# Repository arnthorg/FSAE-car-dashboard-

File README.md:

# A dashboard with rpm bar-graph, gear display, shift-light and oil pressure/  AFR / Speed for RU's 2016 FSAE car 

It's programmed in the arduino environment 

It has:
* engine RPM bargraph, 
* shift light
* OLED display capable if displaying any analog value
* 7-seg gear selected display

Dash-OLED/ contains the main program

PCB/ contains the PCB design

lid/ contains the sketch for the lid that enclosed the electronics

myndir/ contains some images of the project

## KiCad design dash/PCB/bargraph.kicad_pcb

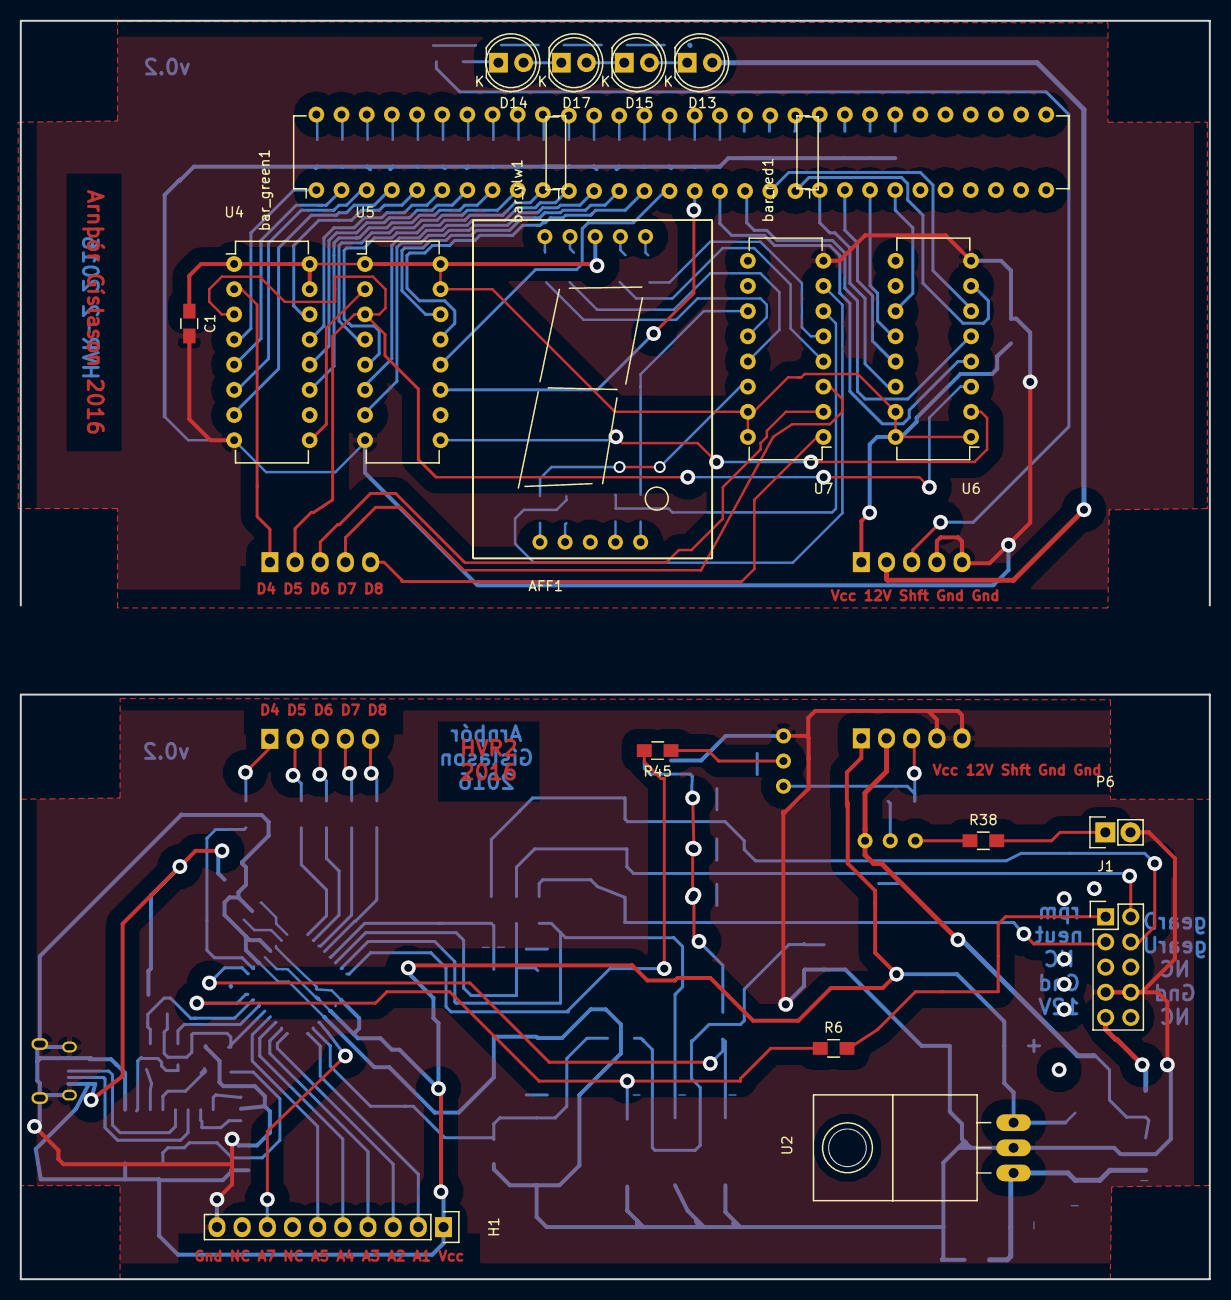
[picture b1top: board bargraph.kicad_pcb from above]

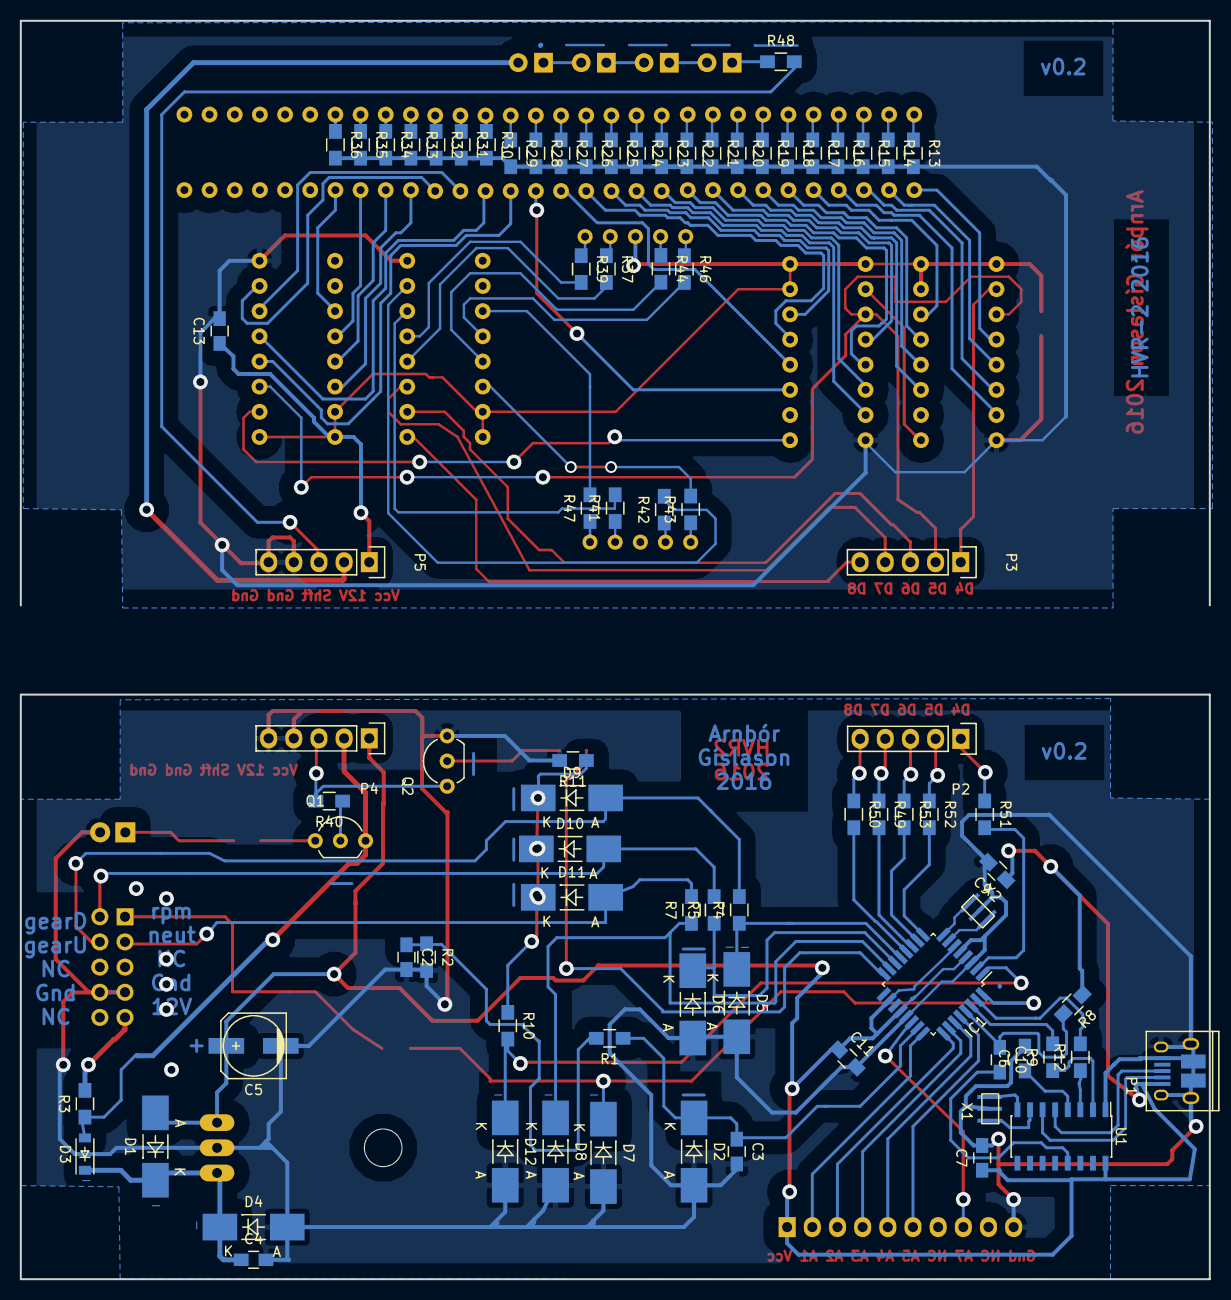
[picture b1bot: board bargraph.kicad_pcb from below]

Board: 2 copper layers, 120.0 x 127.0 mm, 103 parts (83 on the bottom side), 122 nets.

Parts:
AFF1: 7SEGMENTS; 7seg
C1, C6, C7, C9, C10, C11, C13: 100n; C_0805_HandSoldering
C2, C3: C; C_0805_HandSoldering
C4: 470n; C_0805_HandSoldering
C5: 100u; c_elec_6.3x5.8
D1: 1n4007; MELF_Handsoldering
D2, D5, D6, D7, D8, D12: 5.1V; MELF_Handsoldering
D3: D_Schottky_Small; SOD-123
D4: 22V; MELF_Handsoldering
D9, D10, D11: 1n4148; MELF_Handsoldering
D13, D14, D15, D17: LED; LED-5MM
H1: pin_header_10; Pin_Header_Straight_1x10
IC1: ATMEGA328-P; TQFP-32_7x7mm_Pitch0.8mm
J1: DB9; Pin_Header_Straight_2x05
P1: USB_OTG; USB_Micro-B_10103594-0001LF
P2, P4: CONN_01X05; Socket_Strip_Straight_1x05
P3, P5: CONN_01X05; Pin_Header_Straight_1x05
P6: CONN_01X02; Socket_Strip_Straight_1x02
Q1: BC557; TO-92_Inline_Wide
Q2: BC547; TO-92_Inline_Wide
R1, R4, R5, R6, R7, R10: 2k2; R_0805_HandSoldering
R2, R9, R12, R49, R52, R53: 1k; R_0805_HandSoldering
R3: 1; R_0805_HandSoldering
R8, R50: 1kR; R_0805_HandSoldering
R11, R40: 10k; R_0805_HandSoldering
R13, R14, R15, R16, R17, R18, R19, R20, R21, R22, R23, R24, R25, R26, R27, R28, R29, R30, R31, R32, R33, R34, R35, R36, R37, R39, R41, R42, R43, R44, R46, R47: 330; R_0805_HandSoldering
R38: 1R; R_0805_HandSoldering
R45: 2k7; R_0805_HandSoldering
R48: 60R; R_0805_HandSoldering
R51: R; R_0805_HandSoldering
U1: CH340G; SOIC-16_3.9x9.9mm_Pitch1.27mm
U2: LM7805CT; TO-220_Neutral123_Horizontal_LargePads
U4, U5, U6, U7: 74HC4094; DIP-16_W7.62mm
X1, X2: CRYSTAL_SMD; cer_res
bar_green1: DOT-BAR2; DIP-20_W7.62mm
bar_red1: DOT-BAR2; DIP-20_W7.62mm
bar_ylw1: DOT-BAR2; DIP-20_W7.62mm

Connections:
/12vF: D3.2, D13.2, P4.2, P5.2, Q1.3, R3.1
/12vraw: J1.9, R3.2
/A0: C3.1, D2.1, IC1.23, R1.1
/A1: H1.2, IC1.24
/A2: H1.3, IC1.25
/A3: H1.4, IC1.26
/A4: H1.5, IC1.27
/A5: H1.6, IC1.28
/A7: H1.8, IC1.22
/D0: IC1.30, R9.2
/D1: IC1.31, R12.2
/D2: D7.1, IC1.32, R6.1
/D3: D12.1, IC1.1, R10.2
/D4: IC1.2, P3.1, R51.2, U4.2
/D5: IC1.9, P3.2, R52.2, U4.3, U5.3, U6.3
/D6: IC1.10, P3.3, R53.2, U7.2
/D7: IC1.11, P3.4, R49.2, U7.3
/D8: IC1.12, P3.5, R50.2, U7.1
/D9: D5.1, IC1.13, R4.1
/D10: D6.1, IC1.14, R5.1
/D11: D8.1, IC1.15, R7.1
/D12: IC1.16, R45.2
/DTR: C10.2, U1.13
/RST: C10.1, IC1.29, R8.2
/U1_0: U4.4, bar_green1.1
/U1_1: U4.5, bar_green1.2
/U1_2: U4.6, bar_green1.3
/U1_3: U4.7, bar_green1.4
/U1_4: U4.14, bar_green1.5
/U1_5: U4.13, bar_green1.6
/U1_6: U4.12, bar_green1.7
/U1_7: U4.11, bar_green1.8
/U2_0: U5.4, bar_green1.9
/U2_1: U5.5, bar_green1.10
/U2_2: U5.6, bar_ylw1.1
/U2_3: U5.7, bar_ylw1.2
/U2_4: U5.14, bar_ylw1.3
/U2_5: U5.13, bar_ylw1.4
/U2_6: U5.12, bar_ylw1.5
/U2_7: U5.11, bar_ylw1.6
/U3_0: U6.4, bar_ylw1.7
/U3_1: U6.5, bar_ylw1.8
/U3_2: U6.6, bar_ylw1.9
/U3_3: U6.7, bar_ylw1.10
/U3_4: U6.14, bar_red1.1
/U3_5: U6.13, bar_red1.2
/U3_6: U6.12, bar_red1.3
/U3_7: U6.11, bar_red1.4
/Vcc: AFF1.8, C1.1, C5.1, C7.1, C9.1, C11.1, C13.1, D1.2, H1.1, IC1.4, IC1.6, IC1.18, IC1.20, P1.1, P4.1, P5.1, R8.1, U1.16, U2.3, U4.1, U4.15, U4.16, U5.1, U5.15, U5.16, U6.1, U6.15, U6.16, U7.15, U7.16
/extShiftLight: P6.1, R38.2
/gearDown: D10.2, J1.2, R5.2
/gearUp: D9.2, J1.4, R4.2
/intShiftLight: P4.3, P5.3, Q2.1, R40.2, R48.2
/neutral: D11.2, J1.3, R7.2
/oilP: C2.1, R1.2, R2.1
/rpm: J1.1, R6.2
/rx: R9.1, U1.2
/tx: R12.1, U1.3
GNDREF: C1.2, C2.2, C3.2, C4.2, C5.2, C6.2, C7.2, C9.2, C11.2, C13.2, D2.2, D4.2, D5.2, D6.2, D7.2, D8.2, D12.2, H1.10, IC1.3, IC1.5, IC1.21, J1.7, J1.8, P1.5, P1.6, P4.4, P4.5, P5.4, P5.5, P6.2, Q2.3, R2.2, R11.2, R13.2, R14.2, R15.2, R16.2, R17.2, R18.2, R19.2, R20.2, R21.2, R22.2, R23.2, R24.2, R25.2, R26.2, R27.2, R28.2, R29.2, R30.2, R31.2, R32.2, R33.2, R34.2, R35.2, R36.2, U1.1, U2.2, U4.8, U5.8, U6.8, U7.8, X1.2, X2.2
unnamed: AFF1.1, R43.1
unnamed: AFF1.2, R42.1
unnamed: AFF1.4, R41.1
unnamed: AFF1.5, R47.1
unnamed: AFF1.6, R39.1
unnamed: AFF1.7, R37.1
unnamed: AFF1.9, R44.1
unnamed: AFF1.10, R46.1
unnamed: C4.1, D1.1, D3.1, D4.1, U2.1
unnamed: C6.1, U1.4
unnamed: D9.1, D10.1, D11.1, R10.1, R11.1
unnamed: D13.1, D15.2
unnamed: D14.1, R48.1
unnamed: D14.2, D17.1
unnamed: D15.1, D17.2
unnamed: IC1.7, X2.1
unnamed: IC1.8, X2.3
unnamed: P1.2, U1.6
unnamed: P1.3, U1.5
unnamed: P2.1, R51.1
unnamed: P2.2, R52.1
unnamed: P2.3, R53.1
unnamed: P2.4, R49.1
unnamed: P2.5, R50.1
unnamed: Q1.1, R38.1
unnamed: Q1.2, R40.1
unnamed: Q2.2, R45.1
unnamed: R13.1, bar_green1.20
unnamed: R14.1, bar_green1.19
unnamed: R15.1, bar_green1.18
unnamed: R16.1, bar_green1.17
unnamed: R17.1, bar_green1.16
unnamed: R18.1, bar_green1.15
unnamed: R19.1, bar_green1.14
unnamed: R20.1, bar_green1.13
unnamed: R21.1, bar_green1.12
unnamed: R22.1, bar_green1.11
unnamed: R23.1, bar_ylw1.20
unnamed: R24.1, bar_ylw1.19
unnamed: R25.1, bar_ylw1.18
unnamed: R26.1, bar_ylw1.17
unnamed: R27.1, bar_ylw1.16
unnamed: R28.1, bar_ylw1.15
unnamed: R29.1, bar_ylw1.14
unnamed: R30.1, bar_ylw1.13
unnamed: R31.1, bar_ylw1.12
unnamed: R32.1, bar_ylw1.11
unnamed: R33.1, bar_red1.20
unnamed: R34.1, bar_red1.19
unnamed: R35.1, bar_red1.18
unnamed: R36.1, bar_red1.17
unnamed: R37.2, U7.4
unnamed: R39.2, U7.5
unnamed: R41.2, U7.6
unnamed: R42.2, U7.7
unnamed: R43.2, U7.14
unnamed: R44.2, U7.13
unnamed: R46.2, U7.12
unnamed: R47.2, U7.11
unnamed: U1.7, X1.3
unnamed: U1.8, X1.1
unnamed: U4.9, U5.2
unnamed: U5.9, U6.2

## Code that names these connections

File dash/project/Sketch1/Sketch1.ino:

#include "stdbool.h"
#include <avr/wdt.h> // watchdog
#include <EEPROM.h> 
#define interruptPin2 2
#define interruptPin3 3
#define Data 4 // D4
#define CP 5 //   D5
#define Data7 6 //D6
#define CP7 7 
#define Latch7 8 //PORTB tekur við
#define gearUp 9
#define gearDown 10
#define neutral 11 
#define oilP A0
 

const unsigned short MAX_RPM = 9100;
const short BAR_SIZE = 10;
const byte digit[8] = { B00001010, B01100000, B00101010,         //r,1,n,2,3,4,5,E
						B11011010, B11110010, B01100110,
						B10110110, B10011110 };

volatile unsigned long g_lastInterrupt;
volatile unsigned long g_lastInterrupt2;
volatile unsigned short g_pos = 0;
double g_rpm[10] = { 0 };
bool g_barGraphArr[BAR_SIZE] = { 0 };
bool g_periodOn7SegDisp = 0;
volatile short g_selectedGear = 32;


void setup() {

	Serial.begin(9600);
	pinMode(interruptPin2, INPUT);
	pinMode(interruptPin3, INPUT); //external pulldown
	pinMode(neutral, INPUT_PULLUP); //external pulldown
	pinMode(Data, OUTPUT);
	pinMode(CP, OUTPUT);
	pinMode(CP7, OUTPUT);
	pinMode(Data7, OUTPUT);
	pinMode(Latch7, OUTPUT);
	pinMode(gearUp, INPUT);
	pinMode(gearDown, INPUT);
	PORTD &= ~((1 << Data7) | (1 << CP7) | (1 << Latch7)); // unsetting bits, dno if needed
	delay(100); //maybe this delay is important?
	attachInterrupt(digitalPinToInterrupt(interruptPin2), blink, RISING);
	attachInterrupt(digitalPinToInterrupt(interruptPin3), setGear, RISING);
	if (!(PINB & (1 << neutral - 8))) sevenSeg(7); //display E on 7seg
	else {
		g_selectedGear = 2; // 1 being neutral
		sevenSeg(1);
	}
}
// todo: 
// watchdog timer
// skjár
// lesa frá mælum
void loop() {
	
	barGraph(calcRpmAvg());
	//sevenSeg(g_selectedGear); // refresh display periodically
	//Serial.println(g_selectedGear);
}
void setGear() { //int 1
	if (PINB & (1 << (neutral - 8))) {          // 
		g_selectedGear = 2;						//2 being neutral
		return;
	}
	bool gearUpState = (PINB & (1 << (gearUp - 8)));
	bool gearDownState = (PINB & (1 << (gearDown - 8)));
	unsigned long currentInterrupt = micros();
	if ((currentInterrupt - g_lastInterrupt2) > 1.5e5) { //debounce 150ms
		//if ((PINB & (1 << neutral - 8)) && g_selectedGear >6) g_selectedGear = 1; 
		if (gearUpState && g_selectedGear < 6) {
			g_selectedGear++;
		}
		else if (gearDownState && g_selectedGear > 1) {
			g_selectedGear--;
		}
		sevenSeg(g_selectedGear);
		g_lastInterrupt2 = currentInterrupt;
	}
}

void barGraph(int rpm) {
	num2array(rpm);
	for (int iter = 0; iter < BAR_SIZE; iter++) {
		bool x = g_barGraphArr[BAR_SIZE - iter - 1];
		PORTD ^= (-x ^ PORTD) & (1 << Data);
		PORTD |= (1 << CP);
		PORTD &= ~(1 << CP);
	}
}

unsigned int calcRpmAvg() {
	double sum = 0;
	for (int iter = 0; iter <10; iter++) {
		sum += g_rpm[iter];
	}
	return sum / 10;
}

void blink() { // int0
	unsigned long currentInterrupt = micros();
	if ((currentInterrupt - g_lastInterrupt) > 5 * 1000) { //debounce
		calculateRpm(currentInterrupt);
		g_lastInterrupt = currentInterrupt;
	}
}

void calculateRpm(unsigned long currentInterrupt) { //calculates RPM from deltaT 
	float deltaT;
	deltaT = currentInterrupt - g_lastInterrupt;
	deltaT = 1e6 / deltaT;
	deltaT *= 60;
	g_rpm[g_pos] = deltaT;
	g_pos++;
	if (g_pos >9) g_pos = 0;
}

void num2array(double rpm) { // converts rpm to an array of bits to bang into shift registers
	int range = MAX_RPM / BAR_SIZE;
	for (int iter = 0; iter < BAR_SIZE; iter++) {
		if (rpm > range * iter) {
			g_barGraphArr[iter] = 1;
		}
		else g_barGraphArr[iter] = 0;
	}
}
void sevenSeg(short symbol) {
	byte digitTmp = 0;
	if (symbol >6)
		digitTmp = digit[7]; //if symbol is greater than 6 display E
	else {
		digitTmp = digit[symbol];
	}
	digitTmp ^= (-g_periodOn7SegDisp ^ digitTmp) & 1;

	shiftOut(Data7, CP7, LSBFIRST, ~digitTmp);
	PORTB |= 1; //(1<<Latch7-8);
	delayMicroseconds(10); //datasheet segir 200ns min en þarf alveg 10µs t_w
	PORTB &= ~1; //(1<<Latch7-8);
}

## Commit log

2016-04-28 Creating a new repo
2016-04-29 uploading data and new revisions
2016-04-30 Adding measurements
2016-05-01 some changes + new data for TMAP NTC
2016-05-01 one more measurement and new matlab scripts
2016-05-03 fixing comments and formatting
2016-05-03 Updating data and fixing formatting
2016-05-03 Yet again formatting
2016-05-03 temp files?
2016-05-03 adding comments
2016-05-04 rpm mælingar m. interrupt og fleira data
2016-05-05 untested rpm to bit array
2016-05-05 Bargraph works!
2016-05-06 replacing digitalwrite
    to make the code run faster
2016-05-06 Began drawing a schematic for the circuit
2016-05-06 added 7seg out
2016-05-06 a lot of changes and addtions to rpm.ino
    added functions, removed global vars, added functionality etc. etc.
2016-05-07 completed gearcounter
2016-05-07 new file, gearcounter completed
2016-05-09 Bug in code caused the arrays to be too small
2016-05-09 Fixed a bug where the string was wrong
2016-05-09 Migrating to visual studio
2016-05-09 Progress on the schematic
2016-05-09 progress
2016-05-09 moving between folders
2016-05-10 progress + more libs
2016-05-10 Can't be bothered with the watchdog timer
2016-05-11 One of the boards completed at least
2016-05-16 Fixing bugs in the PCB designe
2016-05-16 added shiftLight
2016-06-05 adding stuff
2016-06-05 changing gearup geardown and netural to be active low
2016-06-07 removing debug and tidying up
2016-06-07 Adding code for OLED
2018-04-18 Committing very old uncommited changes
2018-04-18 committing very old unsaved changes
2018-04-19 preparing to remove irrelevant files and commenting code
2018-04-19 removing irrelevant files and adding to gitignore
2018-04-19 removing files
2018-04-19 removing stuff
2018-04-19 moving things around and removing irrelevant stuff
2018-04-19 removing bunch of stuff
2018-04-19 removing irrelevant stuff
2018-04-19 removing .gitignore
2018-04-19 rm .dropbox
